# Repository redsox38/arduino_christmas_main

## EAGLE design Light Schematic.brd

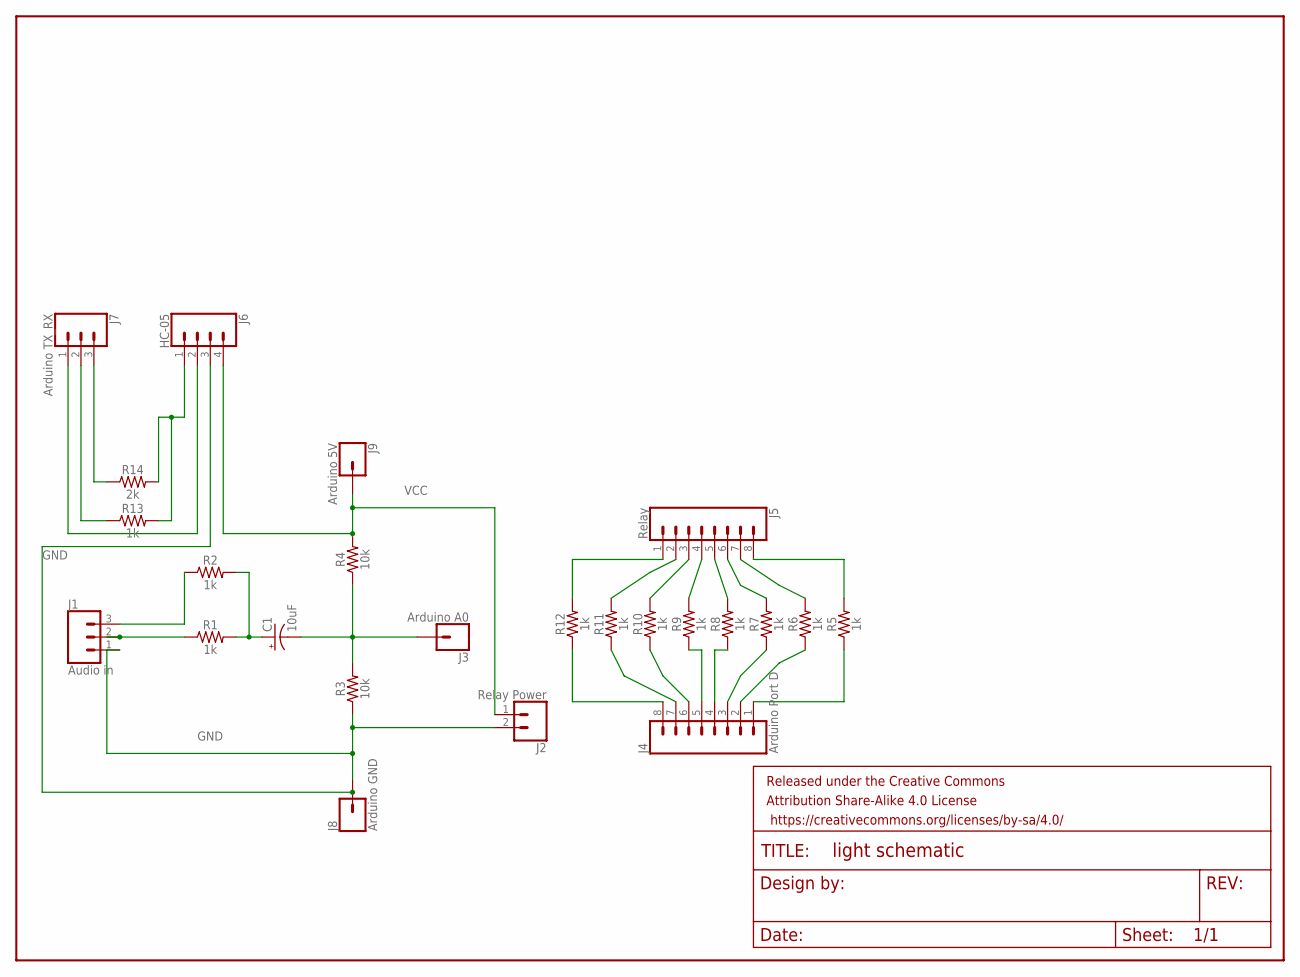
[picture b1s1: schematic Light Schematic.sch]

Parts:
C1: 10uF; CPOL-RADIAL-2.5MM-5MM
FRAME1: FRAME-LETTER; CREATIVE_COMMONS
J1: Audio in; 1X03
J2: Relay Power; 1X02
J3: Arduino A0; 1X01
J4: Arduino Port D; 1X08
J5: Relay; 1X08
J6: HC-05; 1X04
J7: Arduino TX_RX; 1X03
J8: Arduino GND; 1X01
J9: Arduino 5V; 1X01
R1, R2, R5, R6, R7, R8, R9, R10, R11, R12, R13: 1k; AXIAL-0.3
R3, R4: 10k; AXIAL-0.3
R14: 2k; AXIAL-0.3

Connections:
ARD_GND: J7.3, R14.P$1 (1)
ARD_RX: J7.2, R13.P$1 (1)
ARD_TX: J6.2, J7.1
GND: J1.1, J2.2, J6.3, J8.1, R3.P$1 (1)
unnamed: J1.3, R2.P$1 (1)
unnamed: C1.1 (+), R1.P$2 (2), R2.P$2 (2)
unnamed: C1.2 (-), J3.1, R3.P$2 (2), R4.P$1 (1)
unnamed: J5.6, R7.P$2 (2)
unnamed: J5.7, R6.P$2 (2)
unnamed: J5.8, R5.P$2 (2)
unnamed: J4.3, R7.P$1 (1)
unnamed: J4.2, R6.P$1 (1)
unnamed: J4.1, R5.P$1 (1)
R1: J4.8, J5.1, R12.P$1 (1), R12.P$2 (2)
R2: J4.7, J5.2, R11.P$1 (1), R11.P$2 (2)
R3: J4.6, J5.3, R10.P$1 (1), R10.P$2 (2)
R4: J4.5, J5.4, R9.P$1 (1), R9.P$2 (2)
R5: J4.4, J5.5, R8.P$1 (1), R8.P$2 (2)
RT_AUDIO: J1.2, R1.P$1 (1)
RX: J6.1, R13.P$2 (2), R14.P$2 (2)
VCC: J2.1, J6.4, J9.1, R4.P$2 (2)

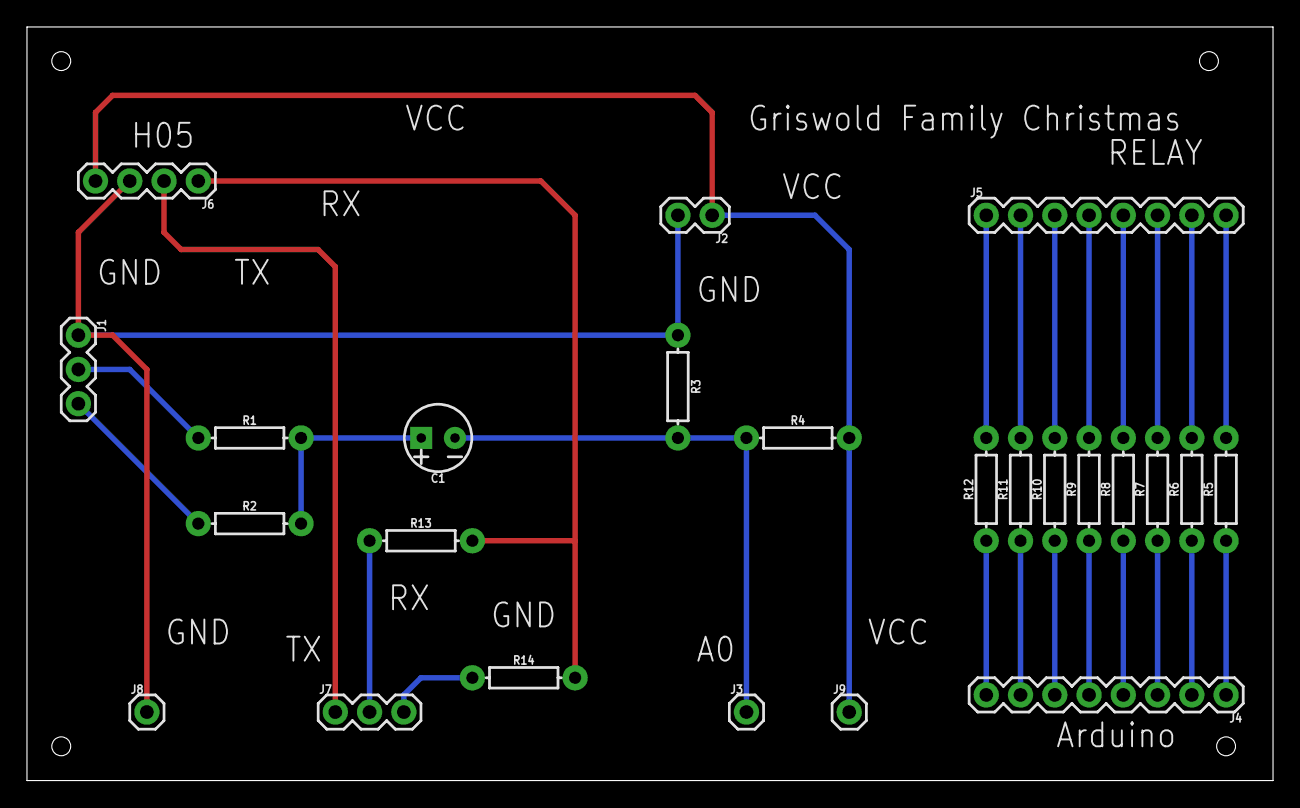
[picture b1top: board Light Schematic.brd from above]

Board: 2 copper layers, 92.4 x 55.9 mm, 25 parts (0 on the bottom side), 21 nets.

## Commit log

2016-12-26 Add board schematic and PCB layout
2017-01-14 Add HC05 setup and sending remote commands for bass/ midrange frequencies
2017-01-16 - Fix bluetooth serial baud rate - add sending signal to other device for bass/low midrange
2017-12-18 Move bass sequence to midrange and add new bass sequence
2017-12-26 Separate frequencies and make bass section match sequence for uno board

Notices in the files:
parts and their libraries:
SparkFun-Capacitors: Licensing: Creative Commons ShareAlike 4.0 International - https://creativecommons.org/licenses/by-sa/4.0
SparkFun-Aesthetics: Released under the Creative Commons Attribution Share-Alike 4.0 License
SparkFun-Aesthetics: https://creativecommons.org/licenses/by-sa/4.0
